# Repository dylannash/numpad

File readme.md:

# Numpad

PCB design implementing an ATmega32u2 and a key matrix

The key matrix has five rows and four columns for a total of 20 keys. I plan on using TMK firmware.

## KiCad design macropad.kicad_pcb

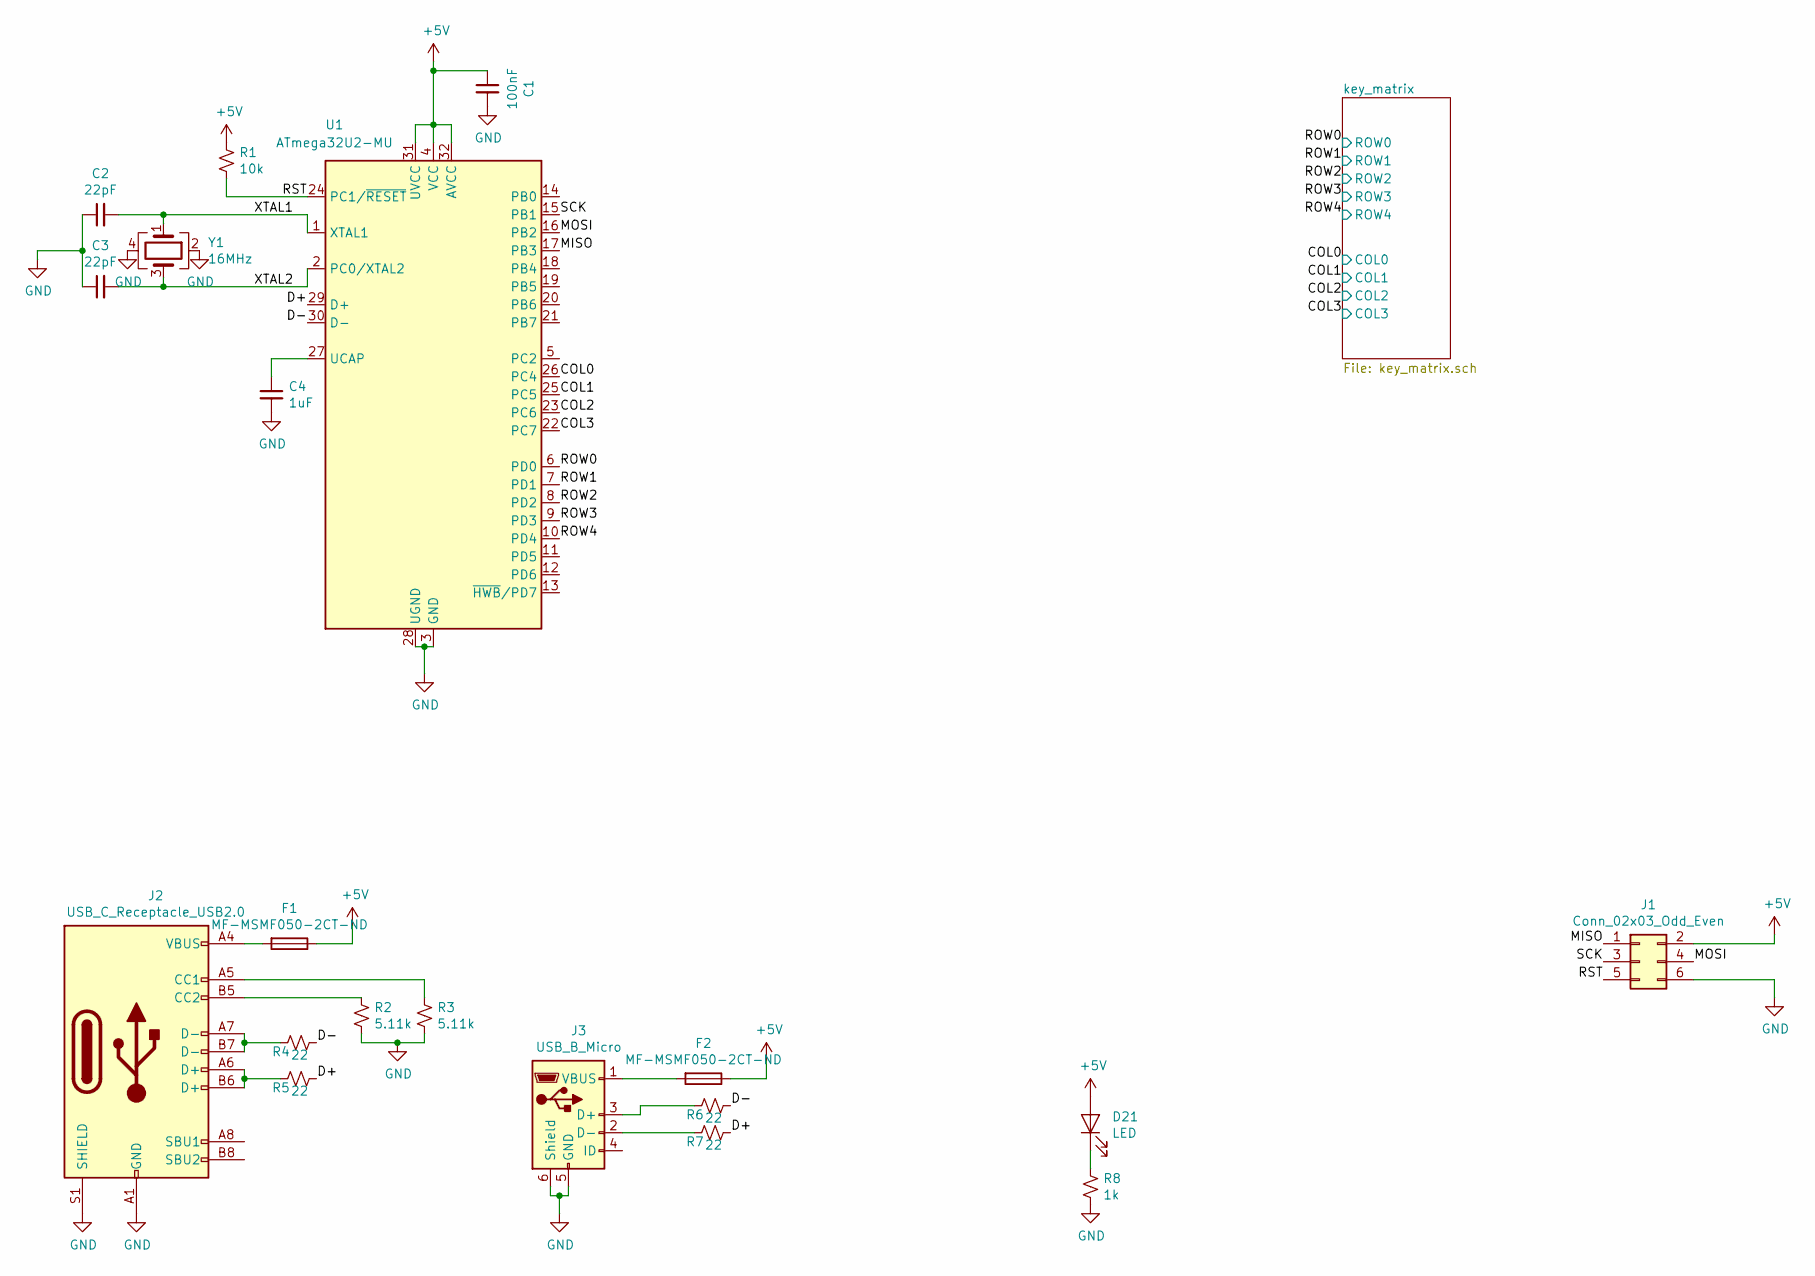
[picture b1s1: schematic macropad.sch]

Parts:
C1: 100nF; C_0603_1608Metric
C2, C3: 22pF; C_0603_1608Metric
C4: 1uF; C_0603_1608Metric_Pad1.05x0.95mm_HandSolder
D21: LED; LED_0603_1608Metric_Pad1.05x0.95mm_HandSolder
F1, F2: MF-MSMF050-2CT-ND; Fuse_1812_4532Metric_Pad1.30x3.40mm_HandSolder
J1: Conn_02x03_Odd_Even; PinHeader_2x03_P1.00mm_Vertical
J2: USB_C_Receptacle_USB2.0; USB_C_Receptacle_GCT_USB4085
J3: USB_B_Micro; USB_Micro-B_Molex-105017-0001
R1: 10k; R_0603_1608Metric_Pad1.05x0.95mm_HandSolder
R2, R3: 5.11k; R_0603_1608Metric_Pad1.05x0.95mm_HandSolder
R4, R5, R6, R7: 22; R_0603_1608Metric_Pad1.05x0.95mm_HandSolder
R8: 1k; R_0603_1608Metric_Pad1.05x0.95mm_HandSolder
U1: ATmega32U2-MU; QFN-32-1EP_5x5mm_P0.5mm_EP3.1x3.1mm
Y1: 16MHz; Crystal_SMD_SeikoEpson_TSX3225-4Pin_3.2x2.5mm_HandSoldering

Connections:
+5V: C1.1, D21.2 (A), F1.1, F2.1, J1.2, R1.2, U1.4 (VCC), U1.31 (UVCC), U1.32 (AVCC)
/COL0: U1.26 (PC4); also elsewhere on the board
/COL1: U1.25 (PC5); also elsewhere on the board
/COL2: U1.23 (PC6); also elsewhere on the board
/COL3: U1.22 (PC7); also elsewhere on the board
/D+: R5.2, R7.2, U1.29 (D+)
/D-: R4.2, R6.2, U1.30 (D-)
/MISO: J1.1, U1.17 (PB3)
/MOSI: J1.4, U1.16 (PB2)
/ROW0: U1.6 (PD0); also elsewhere on the board
/ROW1: U1.7 (PD1); also elsewhere on the board
/ROW2: U1.8 (PD2); also elsewhere on the board
/ROW3: U1.9 (PD3); also elsewhere on the board
/ROW4: U1.10 (PD4); also elsewhere on the board
/RST: J1.5, R1.1, U1.24 (PC1/~RESET)
/SCK: J1.3, U1.15 (PB1)
/XTAL1: C2.2, U1.1 (XTAL1), Y1.1
/XTAL2: C3.2, U1.2 (PC0/XTAL2), Y1.3
GND: C1.2, C2.1, C3.1, C4.2, J1.6, J2.A1 (GND), J2.A12 (GND), J2.B1 (GND), J2.B12 (GND), J2.S1 (SHIELD), J3.5 (GND), J3.6 (Shield), R2.1, R3.1, R8.1, U1.3 (GND), U1.28 (UGND), U1.33 (GND), Y1.2, Y1.4
unnamed: C4.1, U1.27 (UCAP)
unnamed: D21.1 (K), R8.2
unnamed: F1.2, J2.A4 (VBUS), J2.A9 (VBUS), J2.B4 (VBUS), J2.B9 (VBUS)
unnamed: F2.2, J3.1 (VBUS)
unnamed: J2.A5 (CC1), R3.2
unnamed: J2.A6 (D+), J2.B6 (D+), R5.1
unnamed: J2.A7 (D-), J2.B7 (D-), R4.1
unnamed: J2.B5 (CC2), R2.2
unnamed: J3.2 (D-), R7.1
unnamed: J3.3 (D+), R6.1

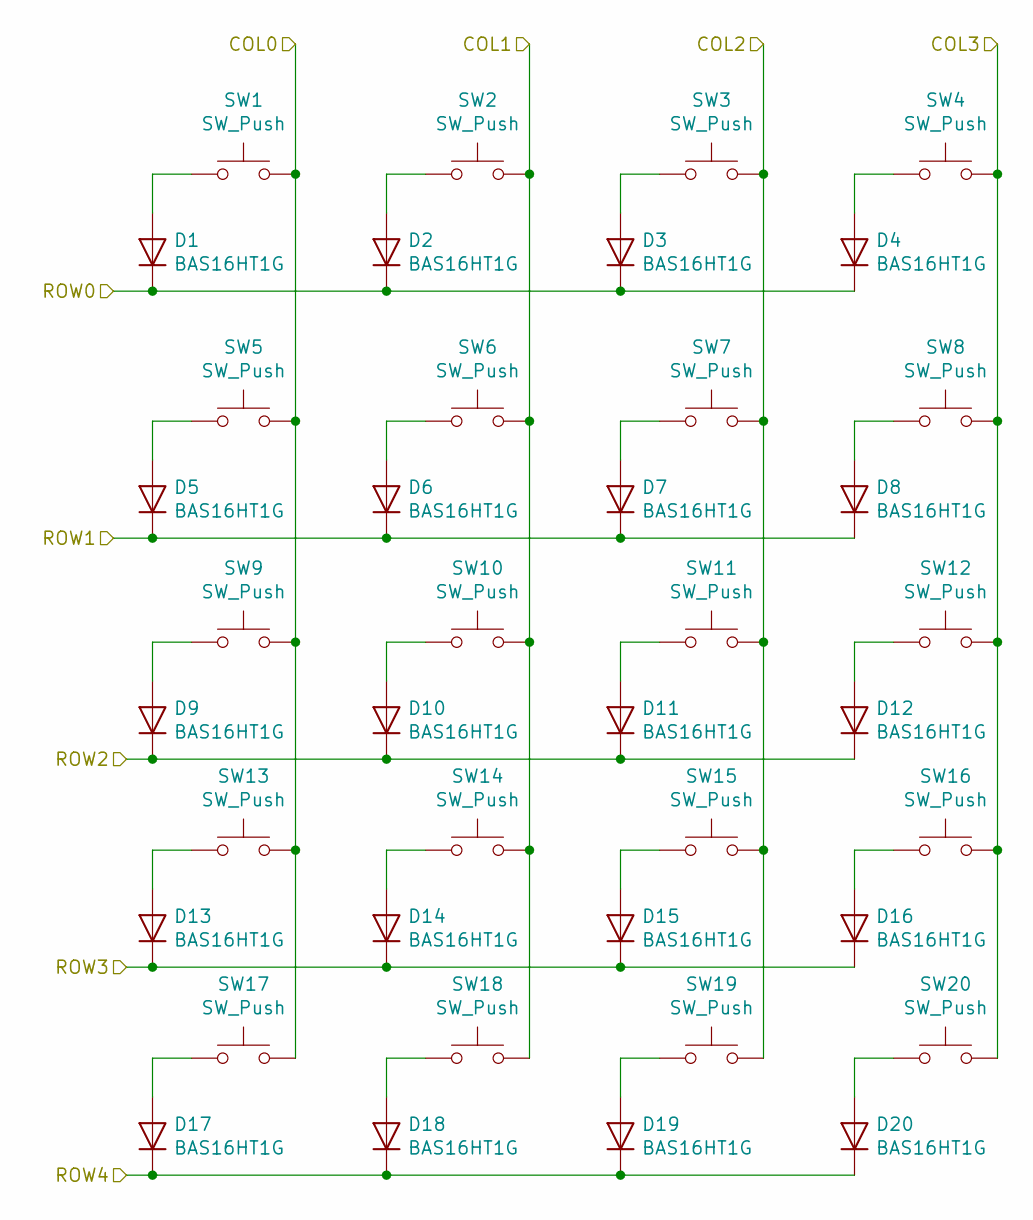
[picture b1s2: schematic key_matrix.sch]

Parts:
D1, D2, D3, D4, D5, D6, D7, D8, D9, D10, D11, D12, D13, D14, D15, D16, D17, D18, D19, D20: BAS16HT1G; D_SOD-323_HandSoldering
SW1, SW2, SW3, SW4, SW5, SW6, SW7, SW8, SW9, SW10, SW11, SW12, SW13, SW14, SW15, SW16, SW17, SW18, SW19, SW20: SW_Push; MX-1U-NoLED

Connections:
/COL0: SW1.2, SW5.2, SW9.2, SW13.2, SW17.2; also elsewhere on the board
/COL1: SW2.2, SW6.2, SW10.2, SW14.2, SW18.2; also elsewhere on the board
/COL2: SW3.2, SW7.2, SW11.2, SW15.2, SW19.2; also elsewhere on the board
/COL3: SW4.2, SW8.2, SW12.2, SW16.2, SW20.2; also elsewhere on the board
/ROW0: D1.1 (K), D2.1 (K), D3.1 (K), D4.1 (K); also elsewhere on the board
/ROW1: D5.1 (K), D6.1 (K), D7.1 (K), D8.1 (K); also elsewhere on the board
/ROW2: D9.1 (K), D10.1 (K), D11.1 (K), D12.1 (K); also elsewhere on the board
/ROW3: D13.1 (K), D14.1 (K), D15.1 (K), D16.1 (K); also elsewhere on the board
/ROW4: D17.1 (K), D18.1 (K), D19.1 (K), D20.1 (K); also elsewhere on the board
unnamed: D1.2 (A), SW1.1
unnamed: D2.2 (A), SW2.1
unnamed: D3.2 (A), SW3.1
unnamed: D4.2 (A), SW4.1
unnamed: D5.2 (A), SW5.1
unnamed: D6.2 (A), SW6.1
unnamed: D7.2 (A), SW7.1
unnamed: D8.2 (A), SW8.1
unnamed: D9.2 (A), SW9.1
unnamed: D10.2 (A), SW10.1
unnamed: D11.2 (A), SW11.1
unnamed: D12.2 (A), SW12.1
unnamed: D13.2 (A), SW13.1
unnamed: D14.2 (A), SW14.1
unnamed: D15.2 (A), SW15.1
unnamed: D16.2 (A), SW16.1
unnamed: D17.2 (A), SW17.1
unnamed: D18.2 (A), SW18.1
unnamed: D19.2 (A), SW19.1
unnamed: D20.2 (A), SW20.1

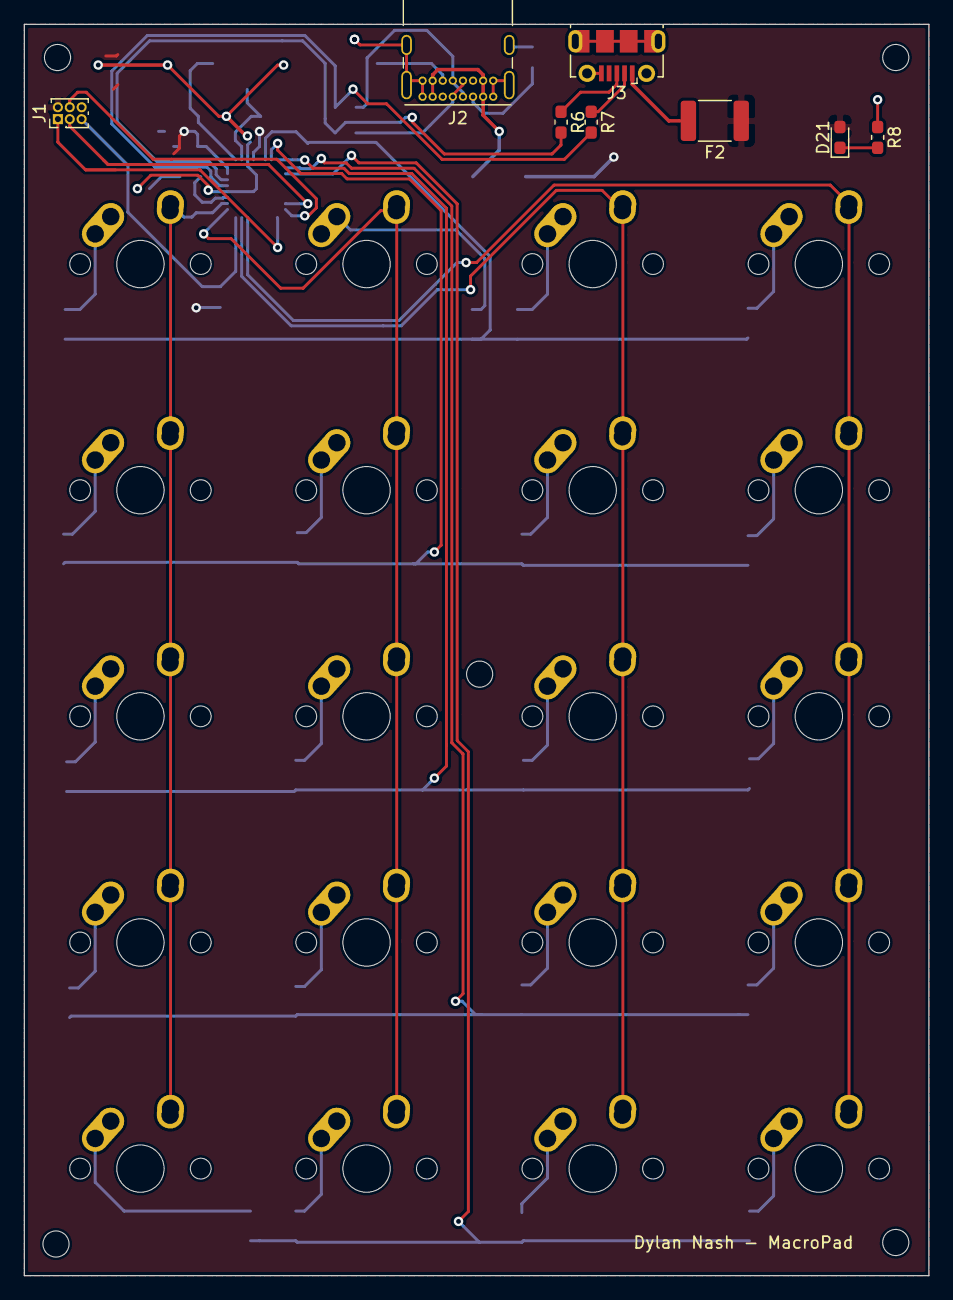
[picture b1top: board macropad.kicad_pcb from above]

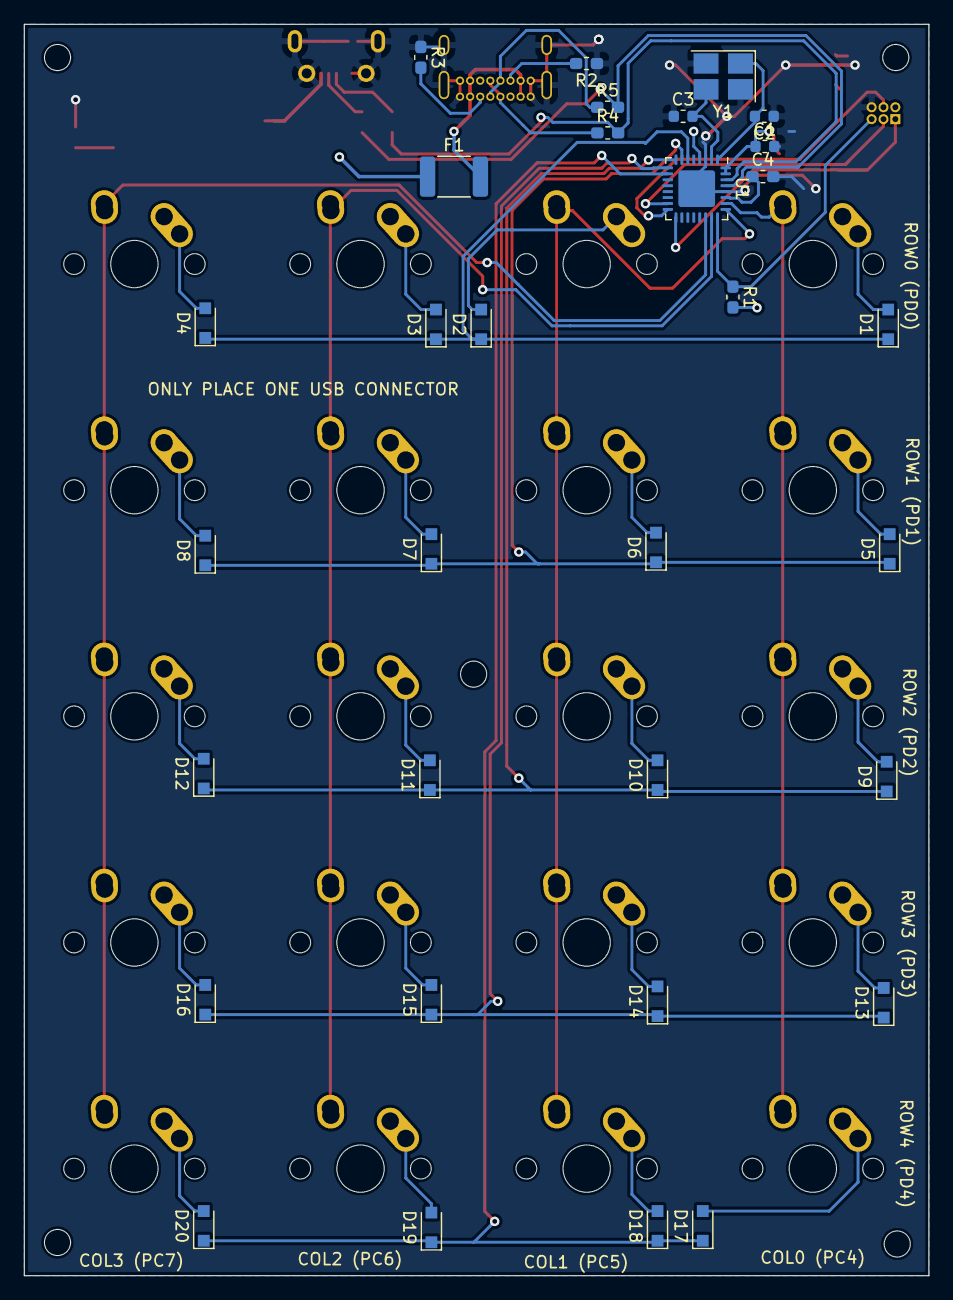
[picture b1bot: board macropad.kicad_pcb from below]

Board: 2 copper layers, 76.2 x 105.4 mm, 60 parts (32 on the bottom side), 49 nets.

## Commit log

2019-10-27 Added PCB Files
